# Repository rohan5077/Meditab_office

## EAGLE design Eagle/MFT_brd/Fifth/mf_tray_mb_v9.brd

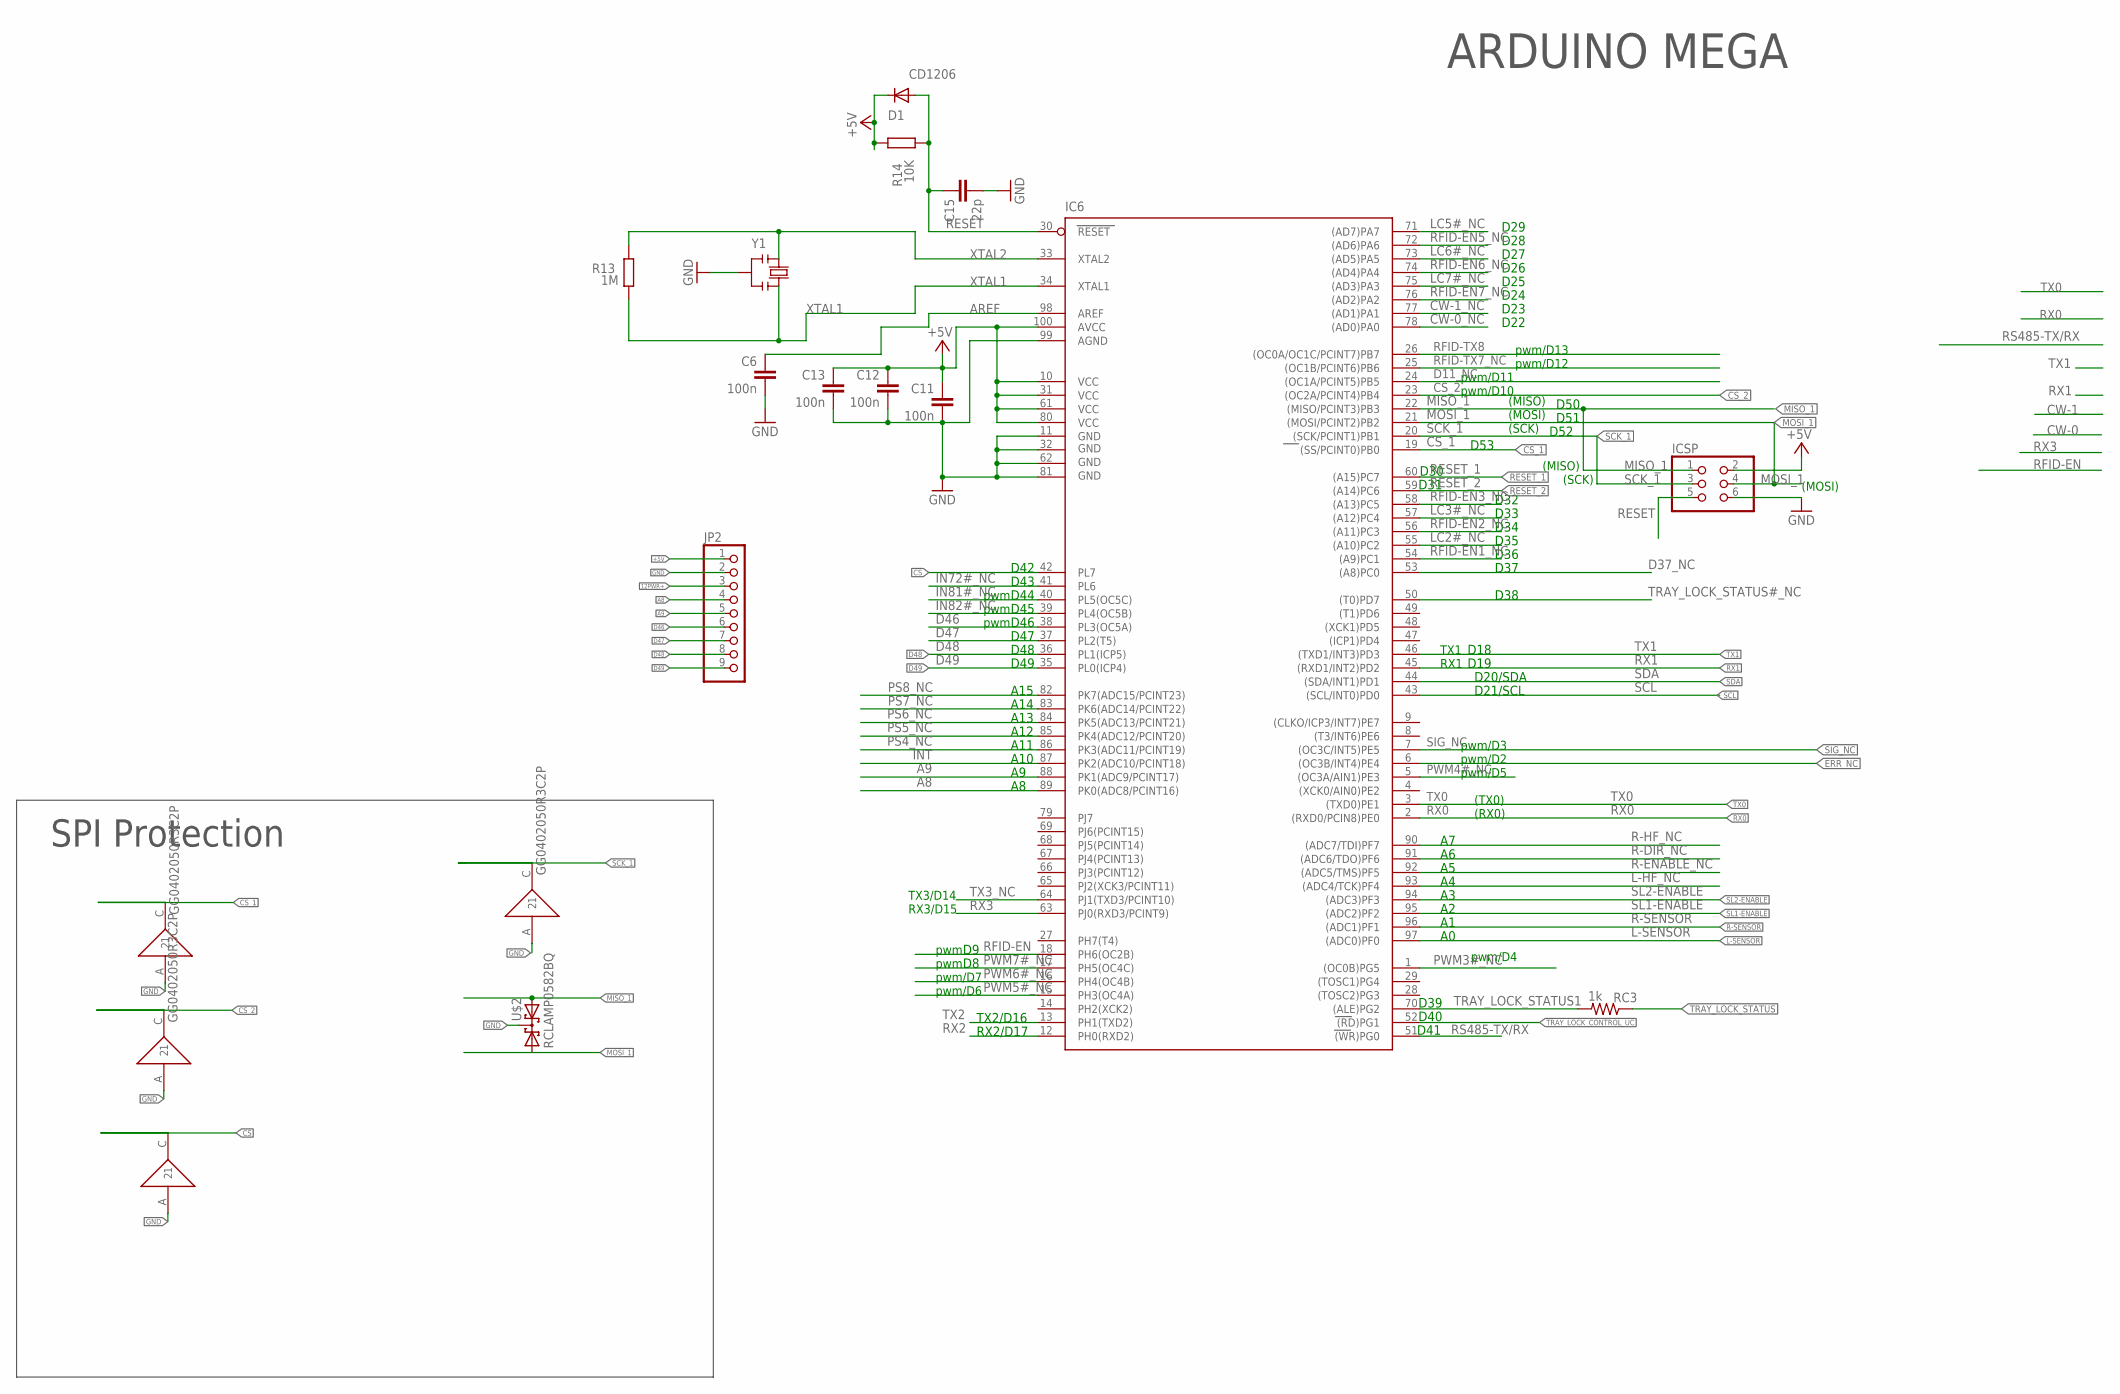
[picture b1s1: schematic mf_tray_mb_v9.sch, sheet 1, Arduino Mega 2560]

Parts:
C6, C11, C12, C13: 100n; C0603-ROUND
C15: 22p; C0603-ROUND
D1: CD1206; MINIMELF
IC6: ATMEGA25602560-16AU; TQFP100
ICSP: PINHD-2X3; 2X03
JP2: PINHD-1X9; 1X09
R13: 1M; R0603-ROUND
R14: 10K; R0603-ROUND
RC3: 1k; R0603@1
U$1, U$3, U$4, U$5: GG0402050R3C2P; 0402
U$2: RCLAMP0582BQ; SOT416
Y1: RESONATORMU; RESONATOR

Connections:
12PWR+: JP2.3; also elsewhere on the board
+5V: C11.1, C12.1, C13.1, D1.C, IC6.10 (VCC), IC6.31 (VCC1), IC6.61 (VCC2), IC6.80 (VCC3), IC6.100 (AVCC), ICSP.2, JP2.1, R14.2; also elsewhere on the board
A8: IC6.89 (PK0(ADC8/PCINT16)), JP2.4
A9: IC6.88 (PK1(ADC9/PCINT17)), JP2.5
AREF: C6.1, IC6.98 (AREF)
CS: IC6.42 (PL7), U$5.C (2); also elsewhere on the board
CS_1: IC6.19 ((SS/PCINT0)PB0), U$3.C (2); also elsewhere on the board
CS_2: IC6.23 ((OC2A/PCINT4)PB4), U$4.C (2); also elsewhere on the board
CW-0_NC: IC6.78 ((AD0)PA0)
CW-1_NC: IC6.77 ((AD1)PA1)
D11_NC: IC6.24 ((OC1A/PCINT5)PB5)
D37_NC: IC6.53 ((A8)PC0)
D46: IC6.38 (PL3(OC5A)), JP2.6
D47: IC6.37 (PL2(T5)), JP2.7
D48: IC6.36 (PL1(ICP5)), JP2.8; also elsewhere on the board
D49: IC6.35 (PL0(ICP4)), JP2.9; also elsewhere on the board
ERR_NC: IC6.6 ((OC3B/INT4)PE4)
GND: C6.2, C11.2, C12.2, C13.2, C15.2, IC6.11 (GND), IC6.32 (GND1), IC6.62 (GND2), IC6.81 (GND3), IC6.99 (AGND), ICSP.6, JP2.2, U$1.A (1), U$2.3 (K1K2), U$3.A (1), U$4.A (1), U$5.A (1), Y1.2; also elsewhere on the board
IN72#_NC: IC6.41 (PL6)
IN81#_NC: IC6.40 (PL5(OC5C))
IN82#_NC: IC6.39 (PL4(OC5B))
INT: IC6.87 (PK2(ADC10/PCINT18)); also elsewhere on the board
L-HF_NC: IC6.93 ((ADC4/TCK)PF4)
L-SENSOR: IC6.97 ((ADC0)PF0); also elsewhere on the board
LC2#_NC: IC6.55 ((A10)PC2)
LC3#_NC: IC6.57 ((A12)PC4)
LC5#_NC: IC6.71 ((AD7)PA7)
LC6#_NC: IC6.73 ((AD5)PA5)
LC7#_NC: IC6.75 ((AD3)PA3)
MISO_1: IC6.22 ((MISO/PCINT3)PB3), ICSP.1, U$2.2 (A2); also elsewhere on the board
MOSI_1: IC6.21 ((MOSI/PCINT2)PB2), ICSP.4, U$2.1 (A1); also elsewhere on the board
PS4_NC: IC6.86 (PK3(ADC11/PCINT19))
PS5_NC: IC6.85 (PK4(ADC12/PCINT20))
PS6_NC: IC6.84 (PK5(ADC13/PCINT21))
PS7_NC: IC6.83 (PK6(ADC14/PCINT22))
PS8_NC: IC6.82 (PK7(ADC15/PCINT23))
PWM3#_NC: IC6.1 ((OC0B)PG5)
PWM4#_NC: IC6.5 ((OC3A/AIN1)PE3)
PWM5#_NC: IC6.15 (PH3(OC4A))
PWM6#_NC: IC6.16 (PH4(OC4B))
PWM7#_NC: IC6.17 (PH5(OC4C))
R-DIR_NC: IC6.91 ((ADC6/TDO)PF6)
R-ENABLE_NC: IC6.92 ((ADC5/TMS)PF5)
R-HF_NC: IC6.90 ((ADC7/TDI)PF7)
R-SENSOR: IC6.96 ((ADC1)PF1); also elsewhere on the board
RESET: C15.1, D1.A, IC6.30 (RESET), ICSP.5, R14.1; also elsewhere on the board
RESET_1: IC6.60 ((A15)PC7); also elsewhere on the board
RESET_2: IC6.59 ((A14)PC6); also elsewhere on the board
RFID-EN: IC6.18 (PH6(OC2B)); also elsewhere on the board
RFID-EN1_NC: IC6.54 ((A9)PC1)
RFID-EN2_NC: IC6.56 ((A11)PC3)
RFID-EN3_NC: IC6.58 ((A13)PC5)
RFID-EN5_NC: IC6.72 ((AD6)PA6)
RFID-EN6_NC: IC6.74 ((AD4)PA4)
RFID-EN7_NC: IC6.76 ((AD2)PA2)
RFID-TX7_NC: IC6.25 ((OC1B/PCINT6)PB6)
RFID-TX8: IC6.26 ((OC0A/OC1C/PCINT7)PB7); also elsewhere on the board
RS485-TX/RX: IC6.51 ((WR)PG0); also elsewhere on the board
RX0: IC6.2 ((RXD0/PCIN8)PE0); also elsewhere on the board
RX1: IC6.45 ((RXD1/INT2)PD2); also elsewhere on the board
RX2: IC6.12 (PH0(RXD2)); also elsewhere on the board
RX3: IC6.63 (PJ0(RXD3/PCINT9)); also elsewhere on the board
SCK_1: IC6.20 ((SCK/PCINT1)PB1), ICSP.3, U$1.C (2); also elsewhere on the board
SCL: IC6.43 ((SCL/INT0)PD0)
SDA: IC6.44 ((SDA/INT1)PD1)
SIG_NC: IC6.7 ((OC3C/INT5)PE5)
SL1-ENABLE: IC6.95 ((ADC2)PF2); also elsewhere on the board
SL2-ENABLE: IC6.94 ((ADC3)PF3)
TRAY_LOCK_CONTROL_UC: IC6.52 ((RD)PG1); also elsewhere on the board
TRAY_LOCK_STATUS: RC3.1; also elsewhere on the board
TRAY_LOCK_STATUS1: IC6.70 ((ALE)PG2), RC3.2
TRAY_LOCK_STATUS#_NC: IC6.50 ((T0)PD7)
TX0: IC6.3 ((TXD0)PE1); also elsewhere on the board
TX1: IC6.46 ((TXD1/INT3)PD3); also elsewhere on the board
TX2: IC6.13 (PH1(TXD2)); also elsewhere on the board
TX3_NC: IC6.64 (PJ1(TXD3/PCINT10))
XTAL1: IC6.34 (XTAL1), R13.1, Y1.3
XTAL2: IC6.33 (XTAL2), R13.2, Y1.1

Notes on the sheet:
pwm/D13
pwm/D12
pwm/D11
pwm/D10
pwm/D3
pwm/D2
pwm/D5
pwm/D4
pwm
pwm/D7
pwm/D6
(TX0)
(RX0)
RX1
TX1
(MISO)
(SCK)
(MOSI)
A10
A11
A12
A13
A14
A15
D49
D48
D47
D46
D45
D44
D43
D42
D30
D31
D32
D33
D34
D35
D36
D37

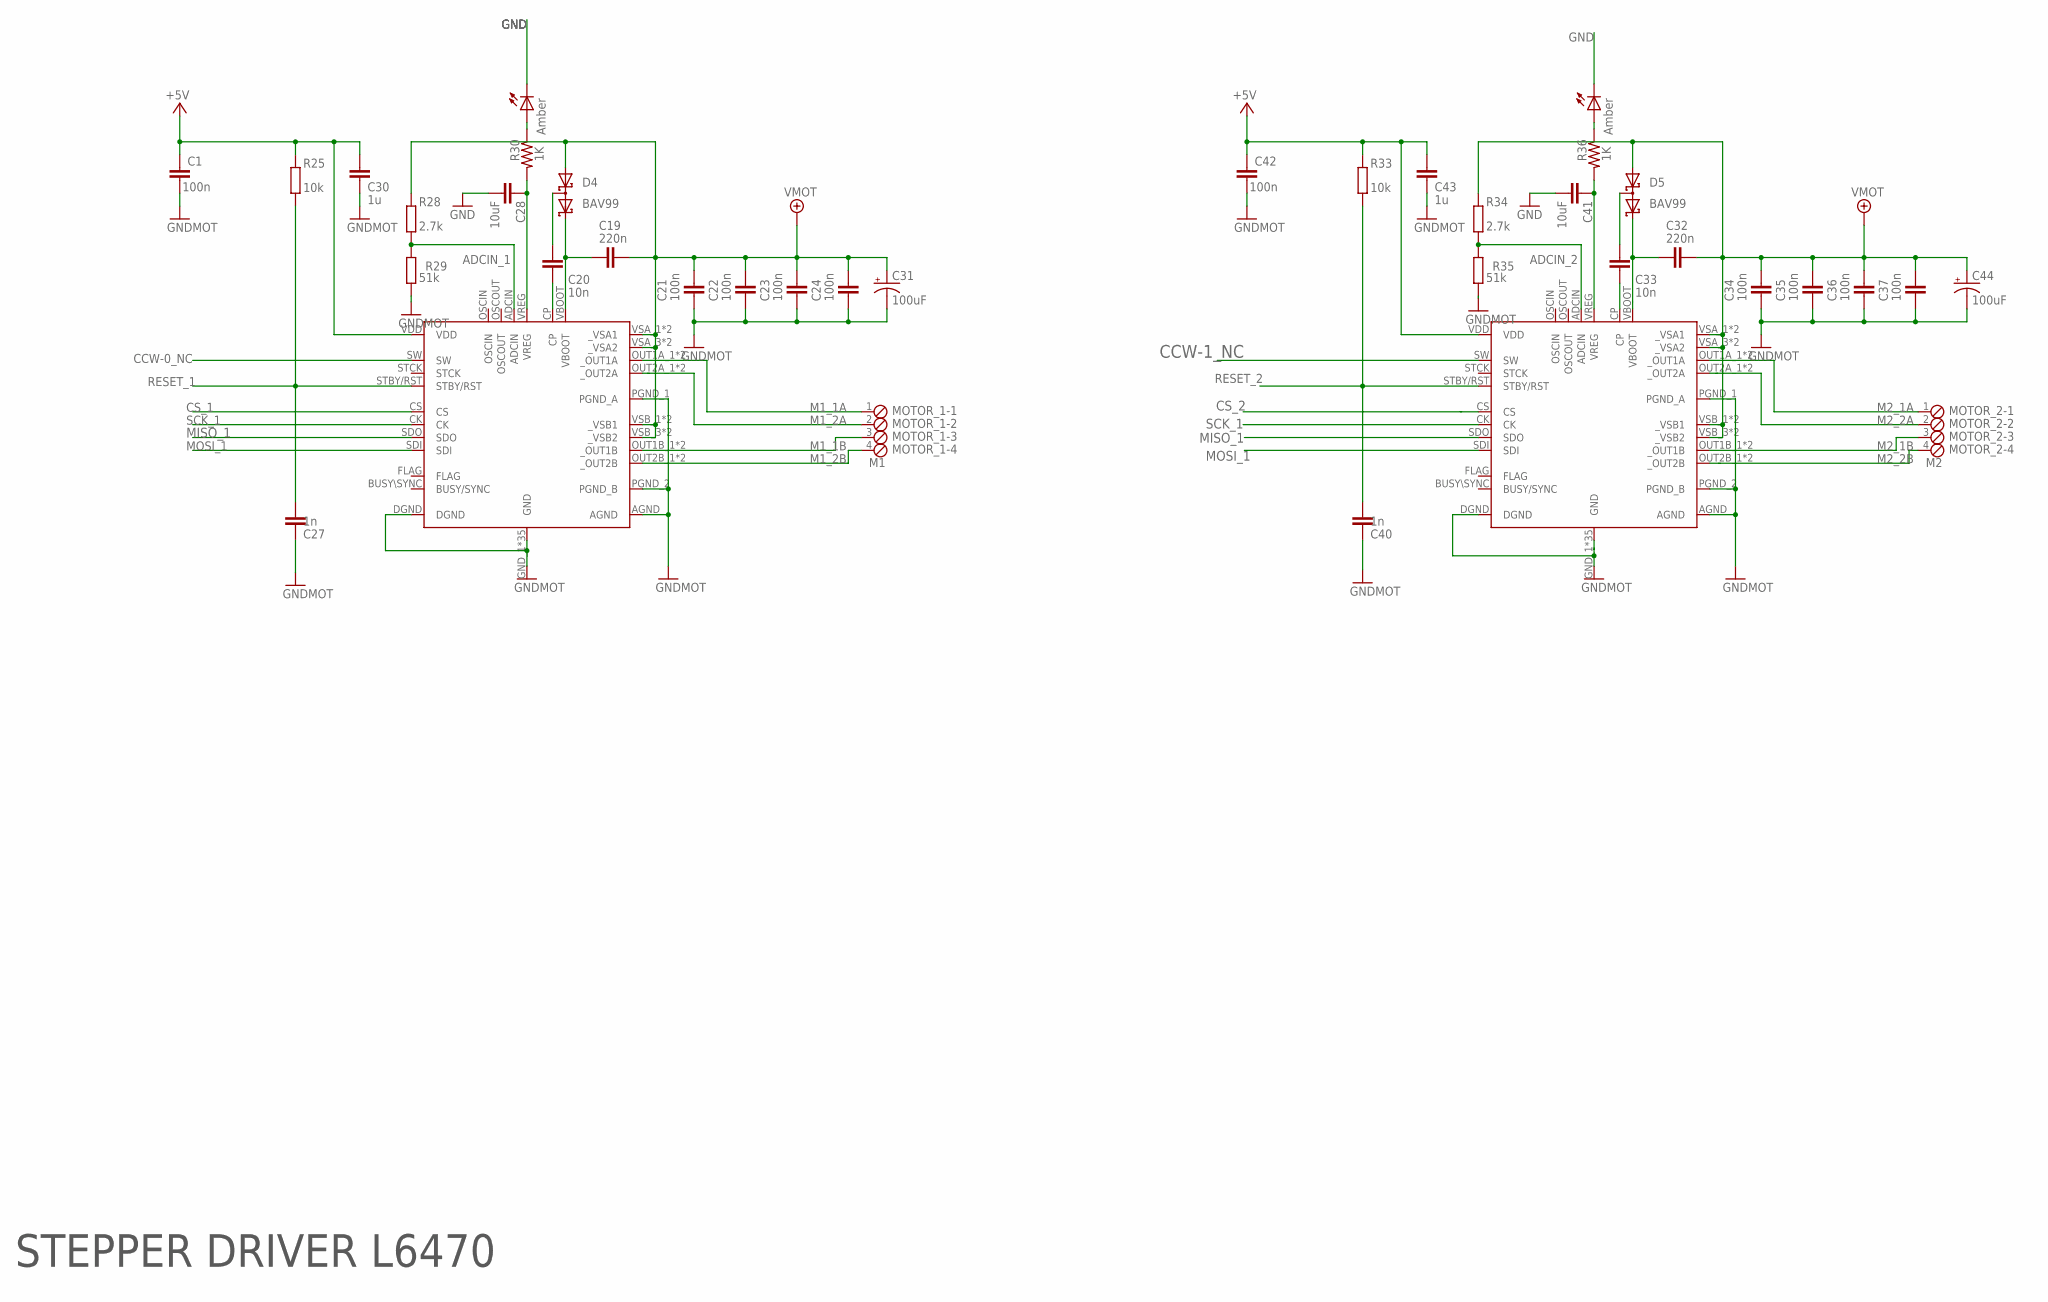
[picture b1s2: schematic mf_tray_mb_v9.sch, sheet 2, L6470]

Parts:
C1, C42: 100n; C0603K; VOLTAGE 25V; PARTNR C0603C104K3RACTU
C19, C32: 220n; C0603K; VOLTAGE 16V; PARTNR 0603YC224MAT2A
C20, C33: 10n; C0603K; VOLTAGE 50V; PARTNR VJ0603Y103KXAAC
C21, C22, C23, C24, C34, C35, C36, C37: 100n; C0603K; VOLTAGE 50V; PARTNR C0603C104K5RACTU
C27, C40: 1n; C0603K; VOLTAGE 10V; PARTNR VJ0603Y102MXQCW1BC
C28, C41: 10uF; C0603; VOLTAGE 6.3V; PARTNR JMK316B7226ML-T
C30, C43: 1u; C0603K; VOLTAGE 16V; PARTNR C0603C105K4RACTU
C31, C44: 100uF; NIC_10X10.5_CAP; MOUSER 647-UUX1J101MNL1GS
D4, D5: BAV99; SOT23; PARTNR BAV99,215
IC$1, IC$2: L6470L6470_4L_2_15; L6470_4L_2_15-POWERSO36
L20, L21: Amber; LED-0603
MOTOR_1: M1; 4POL254
MOTOR_2: M2; 4POL254
R25, R33: 10k; R0603; PARTNR CRCW060339K0FKEA
R28, R34: 2.7k; R0603
R29, R35: 51k; R0603
R30, R36: 1K; 0603-RES

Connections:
12PWR+: C19.2, C21.2, C22.2, C23.2, C24.2, C31.+, C32.2, C34.2, C35.2, C36.2, C37.2, C44.+, D4.1 (A1), D5.1 (A1), IC$1.VSA_1 (_VSA1), IC$1.VSA_2 (_VSA1), IC$1.VSA_3 (_VSA2), IC$1.VSA_4 (_VSA2), IC$1.VSB_1 (_VSB1), IC$1.VSB_2 (_VSB1), IC$1.VSB_3 (_VSB2), IC$1.VSB_4 (_VSB2), IC$2.VSA_1 (_VSA1), IC$2.VSA_2 (_VSA1), IC$2.VSA_3 (_VSA2), IC$2.VSA_4 (_VSA2), IC$2.VSB_1 (_VSB1), IC$2.VSB_2 (_VSB1), IC$2.VSB_3 (_VSB2), IC$2.VSB_4 (_VSB2), R28.2, R34.2; also elsewhere on the board
+5V: C1.2, C30.2, C42.2, C43.2, IC$1.VDD, IC$2.VDD, R25.2, R33.2; also elsewhere on the board
ADCIN_1: IC$1.ADCIN, R28.1, R29.2
ADCIN_2: IC$2.ADCIN, R34.1, R35.2
CCW-0_NC: IC$1.SW
CCW-1_NC: IC$2.SW
CS_1: IC$1.CS; also elsewhere on the board
CS_2: IC$2.CS; also elsewhere on the board
GND: C1.1, C21.1, C22.1, C23.1, C24.1, C27.1, C28.2, C30.1, C31.-, C34.1, C35.1, C36.1, C37.1, C40.1, C41.2, C42.1, C43.1, C44.-, IC$1.AGND, IC$1.DGND, IC$1.GND_1 (GND), IC$1.GND_2 (GND), IC$1.GND_3 (GND), IC$1.GND_4 (GND), IC$1.GND_5 (GND), IC$1.GND_6 (GND), IC$1.GND_7 (GND), IC$1.GND_8 (GND), IC$1.GND_9 (GND), IC$1.GND_10 (GND), IC$1.GND_11 (GND), IC$1.GND_12 (GND), IC$1.GND_13 (GND), IC$1.GND_14 (GND), IC$1.GND_15 (GND), IC$1.GND_16 (GND), IC$1.GND_17 (GND), IC$1.GND_18 (GND), IC$1.GND_19 (GND), IC$1.GND_20 (GND), IC$1.GND_21 (GND), IC$1.GND_22 (GND), IC$1.GND_23 (GND), IC$1.GND_24 (GND), IC$1.GND_25 (GND), IC$1.GND_26 (GND), IC$1.GND_27 (GND), IC$1.GND_28 (GND), IC$1.GND_29 (GND), IC$1.GND_30 (GND), IC$1.GND_31 (GND), IC$1.GND_32 (GND), IC$1.GND_33 (GND), IC$1.GND_34 (GND), IC$1.GND_35 (GND), IC$1.PGND_1 (PGND_A), IC$1.PGND_2 (PGND_B), IC$2.AGND, IC$2.DGND, IC$2.GND_1 (GND), IC$2.GND_2 (GND), IC$2.GND_3 (GND), IC$2.GND_4 (GND), IC$2.GND_5 (GND), IC$2.GND_6 (GND), IC$2.GND_7 (GND), IC$2.GND_8 (GND), IC$2.GND_9 (GND), IC$2.GND_10 (GND), IC$2.GND_11 (GND), IC$2.GND_12 (GND), IC$2.GND_13 (GND), IC$2.GND_14 (GND), IC$2.GND_15 (GND), IC$2.GND_16 (GND), IC$2.GND_17 (GND), IC$2.GND_18 (GND), IC$2.GND_19 (GND), IC$2.GND_20 (GND), IC$2.GND_21 (GND), IC$2.GND_22 (GND), IC$2.GND_23 (GND), IC$2.GND_24 (GND), IC$2.GND_25 (GND), IC$2.GND_26 (GND), IC$2.GND_27 (GND), IC$2.GND_28 (GND), IC$2.GND_29 (GND), IC$2.GND_30 (GND), IC$2.GND_31 (GND), IC$2.GND_32 (GND), IC$2.GND_33 (GND), IC$2.GND_34 (GND), IC$2.GND_35 (GND), IC$2.PGND_1 (PGND_A), IC$2.PGND_2 (PGND_B), L20.C, L21.C, R29.1, R35.1; also elsewhere on the board
M1_1A: IC$1.OUT1A_1 (_OUT1A), IC$1.OUT1A_2 (_OUT1A), MOTOR_1.1
M1_1B: IC$1.OUT1B_1 (_OUT1B), IC$1.OUT1B_2 (_OUT1B), MOTOR_1.3
M1_2A: IC$1.OUT2A_1 (_OUT2A), IC$1.OUT2A_2 (_OUT2A), MOTOR_1.2
M1_2B: IC$1.OUT2B_1 (_OUT2B), IC$1.OUT2B_2 (_OUT2B), MOTOR_1.4
M2_1A: IC$2.OUT1A_1 (_OUT1A), IC$2.OUT1A_2 (_OUT1A), MOTOR_2.1
M2_1B: IC$2.OUT1B_1 (_OUT1B), IC$2.OUT1B_2 (_OUT1B), MOTOR_2.3
M2_2A: IC$2.OUT2A_1 (_OUT2A), IC$2.OUT2A_2 (_OUT2A), MOTOR_2.2
M2_2B: IC$2.OUT2B_1 (_OUT2B), IC$2.OUT2B_2 (_OUT2B), MOTOR_2.4
MISO_1: IC$1.SDO, IC$2.SDO; also elsewhere on the board
MOSI_1: IC$1.SDI, IC$2.SDI; also elsewhere on the board
unnamed: C19.1, D4.2 (C2), IC$1.VBOOT
unnamed: C20.1, IC$1.CP
unnamed: C20.2, D4.3 (C1A2)
unnamed: L20.A, R30.1
unnamed: C28.1, IC$1.VREG, R30.2
unnamed: L21.A, R36.1
unnamed: C32.1, D5.2 (C2), IC$2.VBOOT
unnamed: C33.1, IC$2.CP
unnamed: C33.2, D5.3 (C1A2)
unnamed: C41.1, IC$2.VREG, R36.2
RESET_1: C27.2, IC$1.STBY/RST, R25.1; also elsewhere on the board
RESET_2: C40.2, IC$2.STBY/RST, R33.1; also elsewhere on the board
SCK_1: IC$1.CK, IC$2.CK; also elsewhere on the board

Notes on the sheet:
STEPPER DRIVER L6470

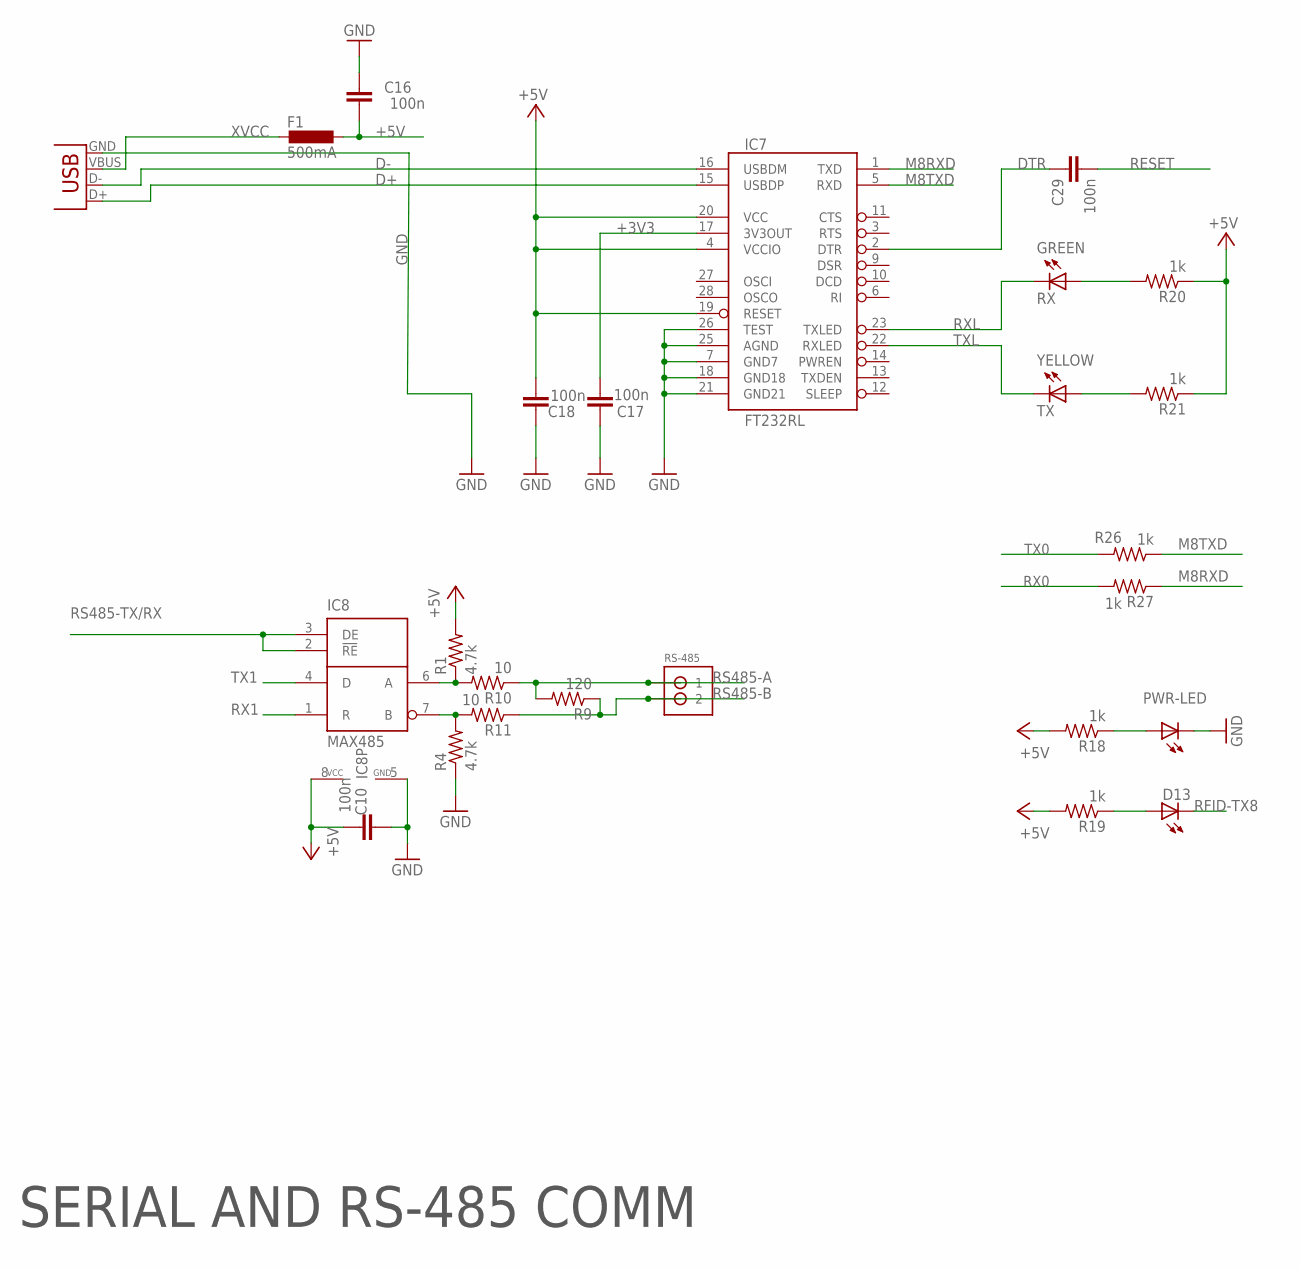
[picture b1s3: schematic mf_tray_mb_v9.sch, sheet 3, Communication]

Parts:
C10, C17, C18, C29: 100n; C0603-ROUND
C16: 100n; C0603
D13: LEDCHIPLED_0603; CHIPLED_0603
F1: 500mA; L1812
IC7: FT232RL; SSOP28DB
IC8: MAX485; SO-08
PWR-LED: LEDCHIPLED_0603; CHIPLED_0603
R1, R4: 4.7k; R0603@1
R9: 120; R0603@1
R10, R11: 10; R0603@1
R18, R19, R20, R21, R26, R27: 1k; R0603@1
RS-485: JST-PH_2-PIN_HEADER; JST_B2B-PH_HEADER
RX: GREEN; CHIPLED_0603
TX: YELLOW; CHIPLED_0603
USB: USB; USB-B-PTH-VERTICAL

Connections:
+3V3: C17.2, IC7.17 (3V3OUT); also elsewhere on the board
+5V: C10.1, C16.1, C18.1, F1.1, IC7.4 (VCCIO), IC7.19 (RESET), IC7.20 (VCC), IC8.8 (VCC), R1.2, R18.2, R19.2, R20.1, R21.1; also elsewhere on the board
D+: IC7.15 (USBDP), USB.D+
D-: IC7.16 (USBDM), USB.D-
DTR: C29.1, IC7.2 (DTR)
GND: C10.2, C16.2, C17.1, C18.2, IC7.7 (GND7), IC7.18 (GND18), IC7.21 (GND21), IC7.25 (AGND), IC7.26 (TEST), IC8.5 (GND), PWR-LED.C, R4.1, USB.GND; also elsewhere on the board
M8RXD: IC7.1 (TXD), R27.1
M8TXD: IC7.5 (RXD), R26.1
unnamed: PWR-LED.A, R18.1
unnamed: D13.A, R19.1
unnamed: R21.2, TX.A
unnamed: IC8.6 (A), R1.1, R10.2
unnamed: IC8.7 (B), R4.2, R11.2
unnamed: R20.2, RX.A
RESET: C29.2; also elsewhere on the board
RFID-TX8: D13.C; also elsewhere on the board
RS485-A: R9.2, R10.1, RS-485.P1 (1); also elsewhere on the board
RS485-B: R9.1, R11.1, RS-485.P2 (2); also elsewhere on the board
RS485-TX/RX: IC8.2 (!RE), IC8.3 (DE); also elsewhere on the board
RX0: R27.2; also elsewhere on the board
RX1: IC8.1 (R); also elsewhere on the board
RXL: IC7.23 (TXLED), RX.C
TX0: R26.2; also elsewhere on the board
TX1: IC8.4 (D); also elsewhere on the board
TXL: IC7.22 (RXLED), TX.C
XVCC: F1.2, USB.VBUS

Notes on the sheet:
SERIAL AND RS-485 COMM

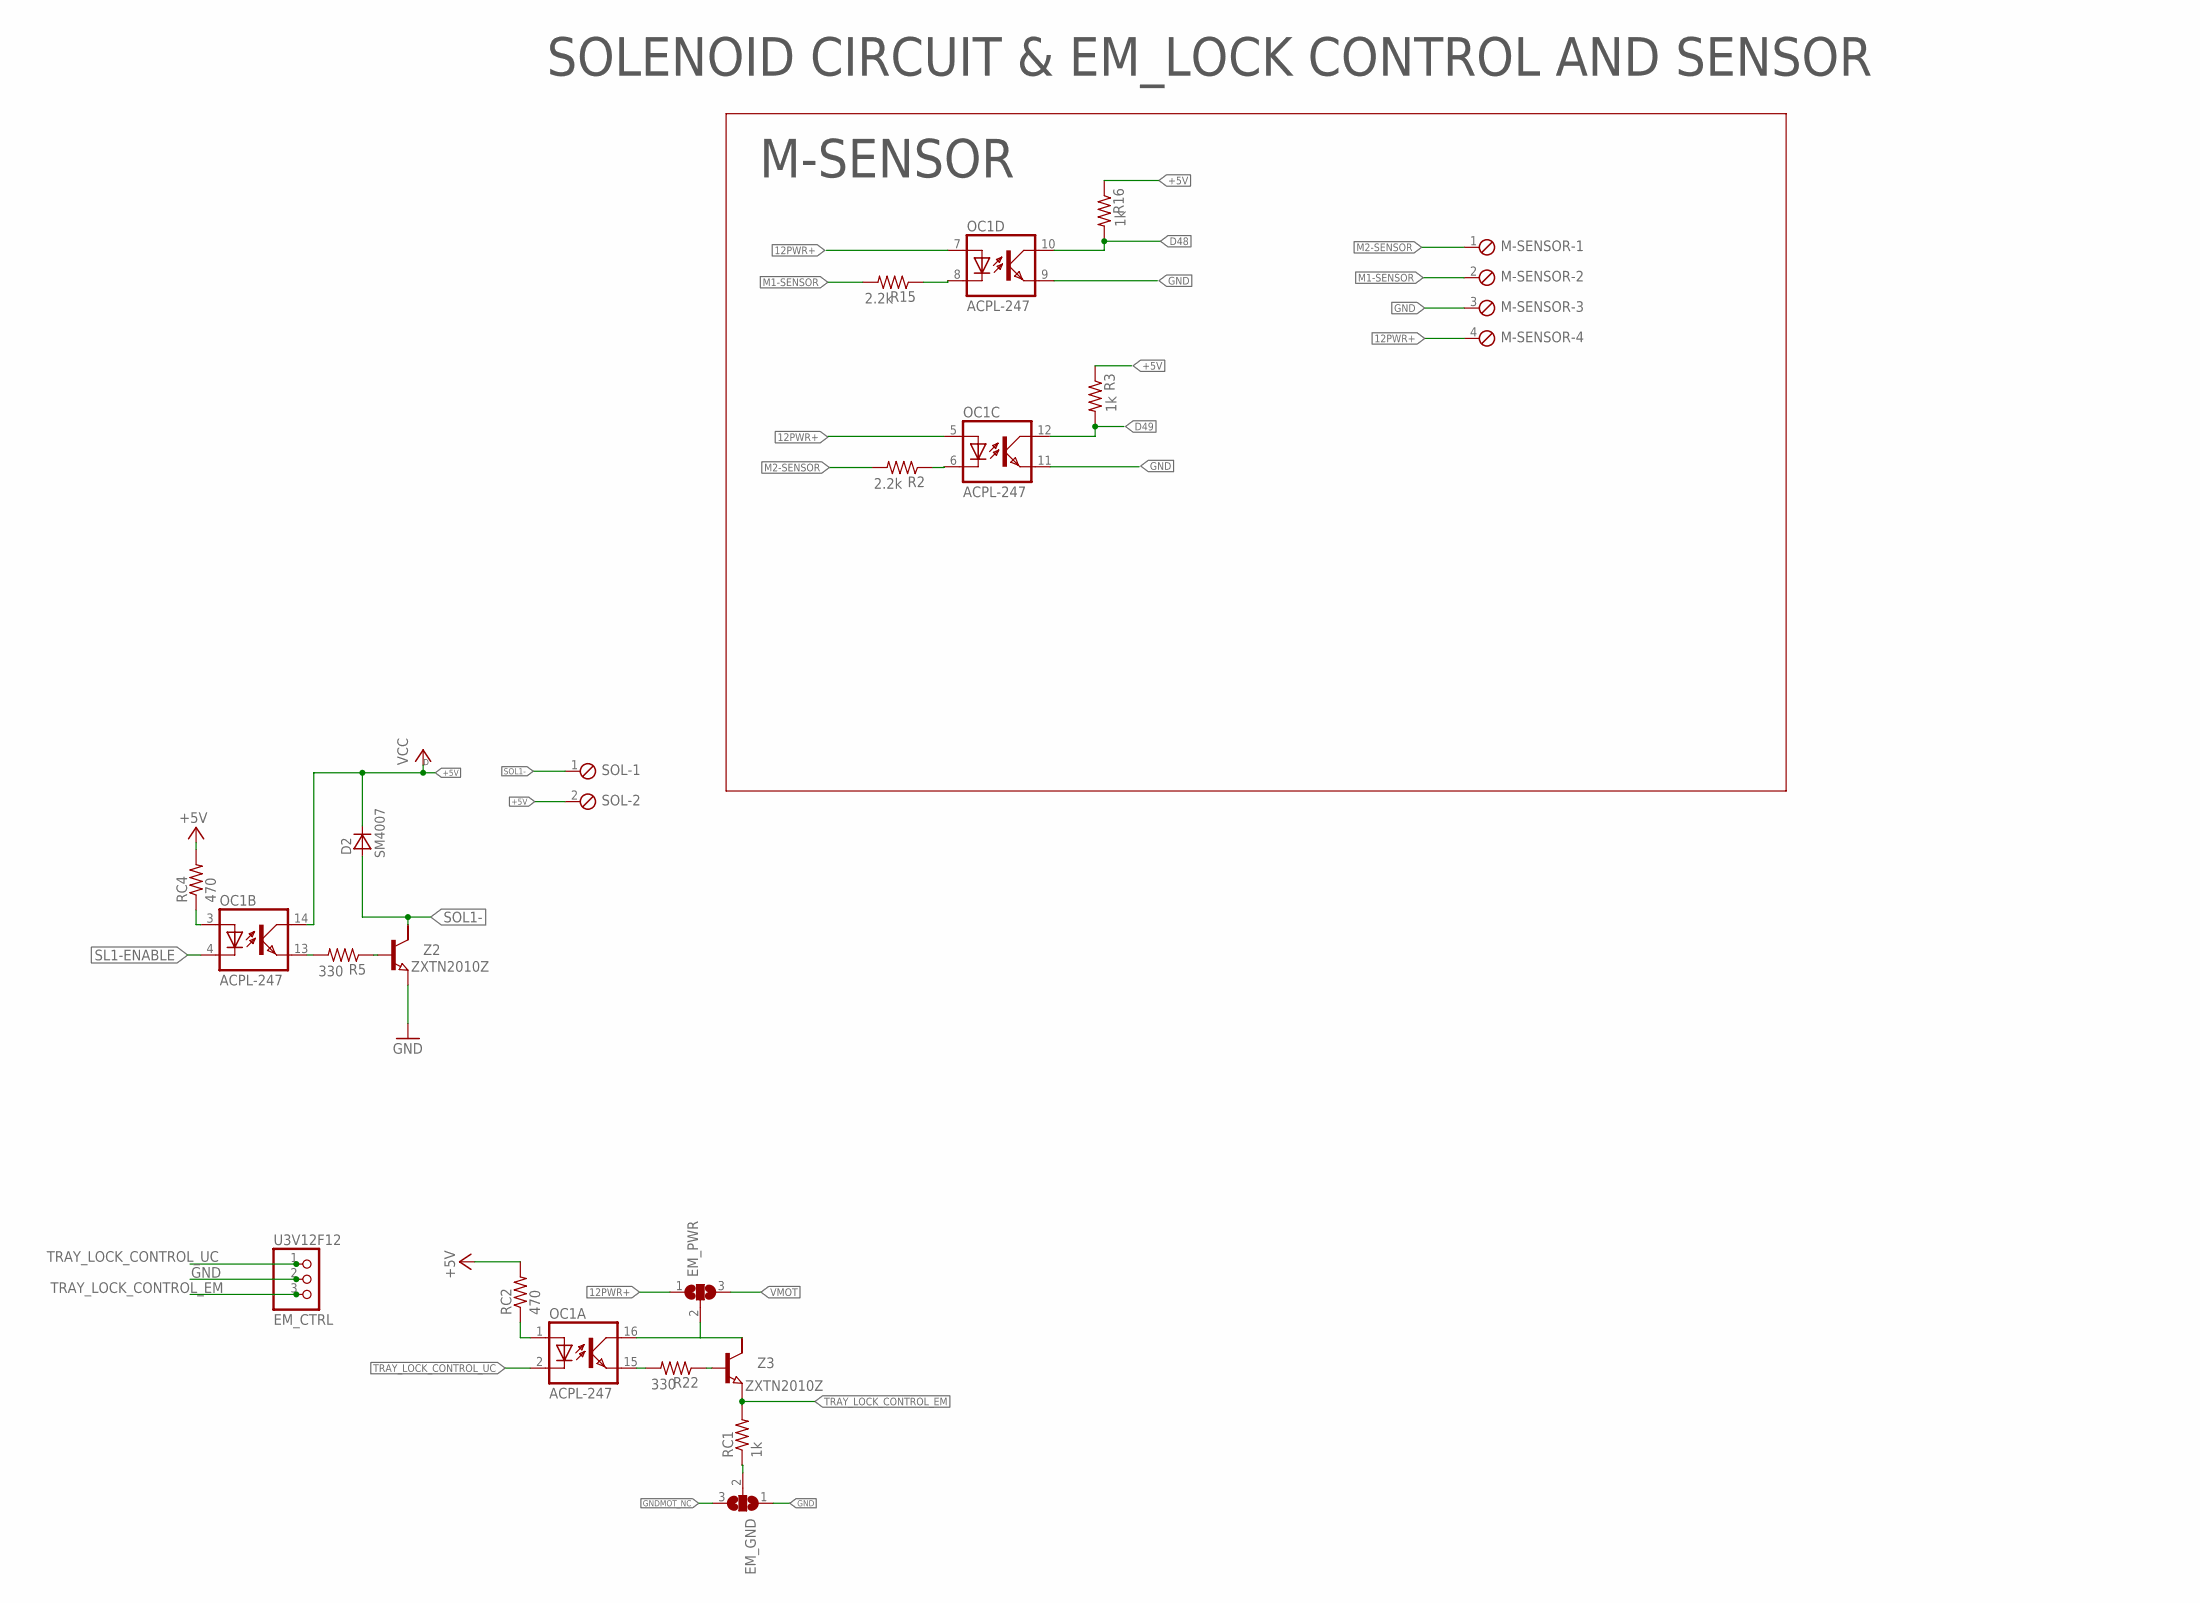
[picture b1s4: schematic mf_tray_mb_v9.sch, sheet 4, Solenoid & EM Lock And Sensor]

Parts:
D2: SM4007; MELF-MLL41
EM_GND: SJ2WW; SJ_2W
EM_PWR: SJ2WW; SJ_2W
M-SENSOR: MPT4; 4POL254
OC1: ACPL-247; SOP16
R2, R15: 2.2k; R0603@1
R3, R16: 1k; R0603@1
R5, R22: 330; R0603@1
RC1: 1k; R0603@1
RC2, RC4: 470; R0603@1
SOL: MPT2; 2POL254
U3V12F12: EM_CTRL; 1X03
Z2, Z3: ZXTN2010Z; SOT89

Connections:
12PWR+: EM_PWR.1, M-SENSOR.4, OC1.5 (A), OC1.7 (A); also elsewhere on the board
+5V: D2.C, OC1.14 (COL), R3.1, R16.1, RC2.2, RC4.2, SOL.2; also elsewhere on the board
D48: OC1.10 (COL), R16.2; also elsewhere on the board
D49: OC1.12 (COL), R3.2; also elsewhere on the board
GND: EM_GND.1, M-SENSOR.3, OC1.9 (EMIT), OC1.11 (EMIT), U3V12F12.2, Z2.3 (E); also elsewhere on the board
GNDMOT_NC: EM_GND.3; also elsewhere on the board
M1-SENSOR: M-SENSOR.2, R15.2
M2-SENSOR: M-SENSOR.1, R2.2
unnamed: OC1.1 (A), RC2.1
unnamed: OC1.15 (EMIT), R22.2
unnamed: OC1.3 (A), RC4.1
unnamed: OC1.13 (EMIT), R5.2
unnamed: R5.1, Z2.1 (B)
unnamed: OC1.8 (C), R15.1
unnamed: OC1.6 (C), R2.1
unnamed: EM_PWR.2, OC1.16 (COL), Z3.2 (C)
unnamed: R22.1, Z3.1 (B)
unnamed: EM_GND.2, RC1.1
SL1-ENABLE: OC1.4 (C); also elsewhere on the board
SOL1-: D2.A, SOL.1, Z2.2 (C)
TRAY_LOCK_CONTROL_EM: RC1.2, U3V12F12.3, Z3.3 (E); also elsewhere on the board
TRAY_LOCK_CONTROL_UC: OC1.2 (C), U3V12F12.1; also elsewhere on the board
VMOT: EM_PWR.3; also elsewhere on the board

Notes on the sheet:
SOLENOID CIRCUIT & EM_LOCK CONTROL AND SENSOR
M-SENSOR

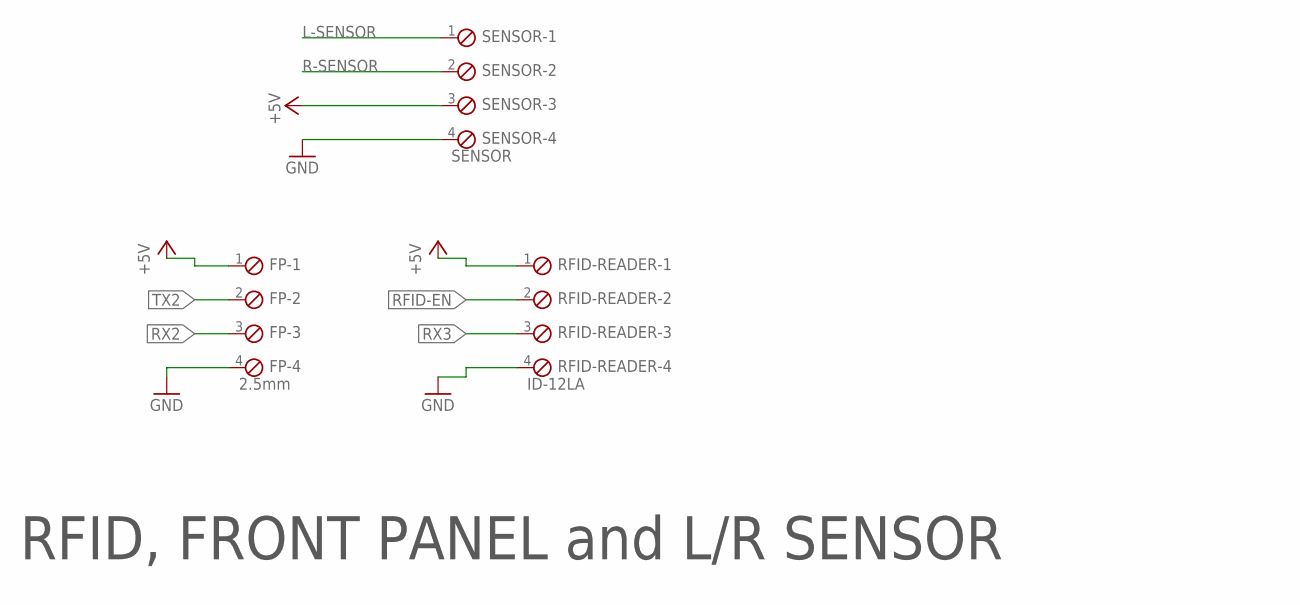
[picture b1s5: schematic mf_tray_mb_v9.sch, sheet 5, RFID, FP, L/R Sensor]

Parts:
FP: 2.5mm; 4POL254
RFID-READER: ID-12LA; 4POL254
SENSOR: SENSOR; 4POL254

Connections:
+5V: FP.1, RFID-READER.1, SENSOR.3; also elsewhere on the board
GND: FP.4, RFID-READER.4, SENSOR.4; also elsewhere on the board
L-SENSOR: SENSOR.1; also elsewhere on the board
R-SENSOR: SENSOR.2; also elsewhere on the board
RFID-EN: RFID-READER.2; also elsewhere on the board
RX2: FP.3; also elsewhere on the board
RX3: RFID-READER.3; also elsewhere on the board
TX2: FP.2; also elsewhere on the board

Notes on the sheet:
RFID, FRONT PANEL and L/R SENSOR

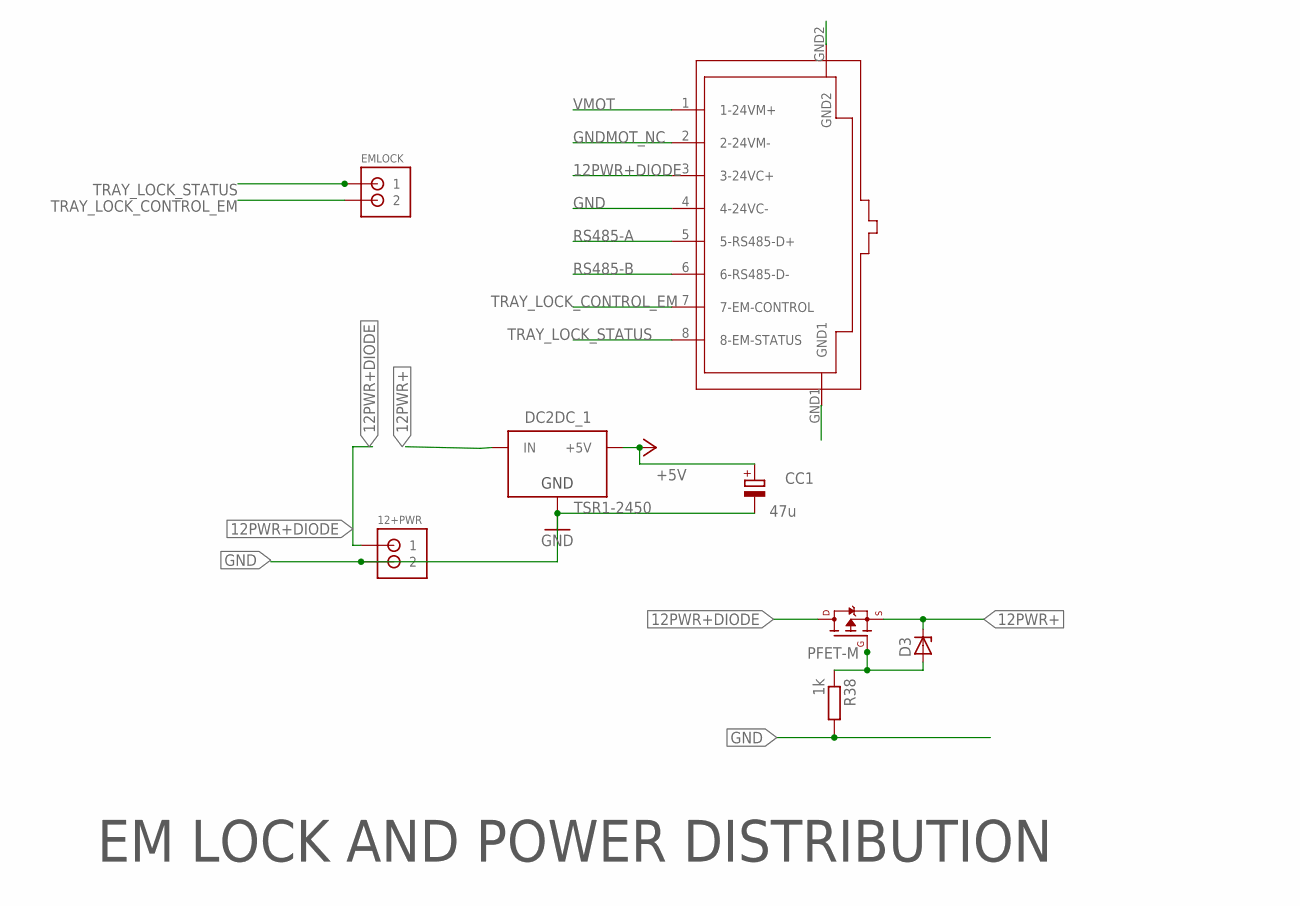
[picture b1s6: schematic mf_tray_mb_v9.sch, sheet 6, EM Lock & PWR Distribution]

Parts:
12+PWR: JST-PH_2-PIN_HEADER; JST_B2B-PH_HEADER
CC1: 47u; PANASONIC_D
D3: 1SMA5925BT3G; DO214AC
DC2DC_1: TSR1-2450; TSR-1
EMLOCK: JST-PH_2-PIN_HEADER; JST_B2B-PH_HEADER
PFET-M: FQP47P06NORMAL; FQP47P06-NORMAL
R38: 1k; R0603
U$10: RJ45-TOP-1-406541-1-CAN-MB; RJ45-TOP

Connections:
12PWR+: D3.C, DC2DC_1.1 (IN), PFET-M.3 (S); also elsewhere on the board
12PWR+DIODE: 12+PWR.P1 (1), PFET-M.2 (D), U$10.3 (3-24VC+)
+5V: CC1.+, DC2DC_1.3 (+5V); also elsewhere on the board
GND: 12+PWR.P2 (2), CC1.-, DC2DC_1.2 (GND), R38.2, U$10.4 (4-24VC-), U$10.GND1, U$10.GND2; also elsewhere on the board
GNDMOT_NC: U$10.2 (2-24VM-); also elsewhere on the board
unnamed: D3.A, PFET-M.1 (G), R38.1
RS485-A: U$10.5 (5-RS485-D+); also elsewhere on the board
RS485-B: U$10.6 (6-RS485-D-); also elsewhere on the board
TRAY_LOCK_CONTROL_EM: EMLOCK.P2 (2), U$10.7 (7-EM-CONTROL); also elsewhere on the board
TRAY_LOCK_STATUS: EMLOCK.P1 (1), U$10.8 (8-EM-STATUS); also elsewhere on the board
VMOT: U$10.1 (1-24VM+); also elsewhere on the board

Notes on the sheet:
EM LOCK AND POWER DISTRIBUTION

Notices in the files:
parts and their libraries:
SparkFun-Connectors: Licensing: Creative Commons ShareAlike 4.0 International - https://creativecommons.org/licenses/by-sa/4.0
SparkFun-Capacitors: Licensing: CC v3.0 Share-Alike You are welcome to use this library for commercial purposes.
